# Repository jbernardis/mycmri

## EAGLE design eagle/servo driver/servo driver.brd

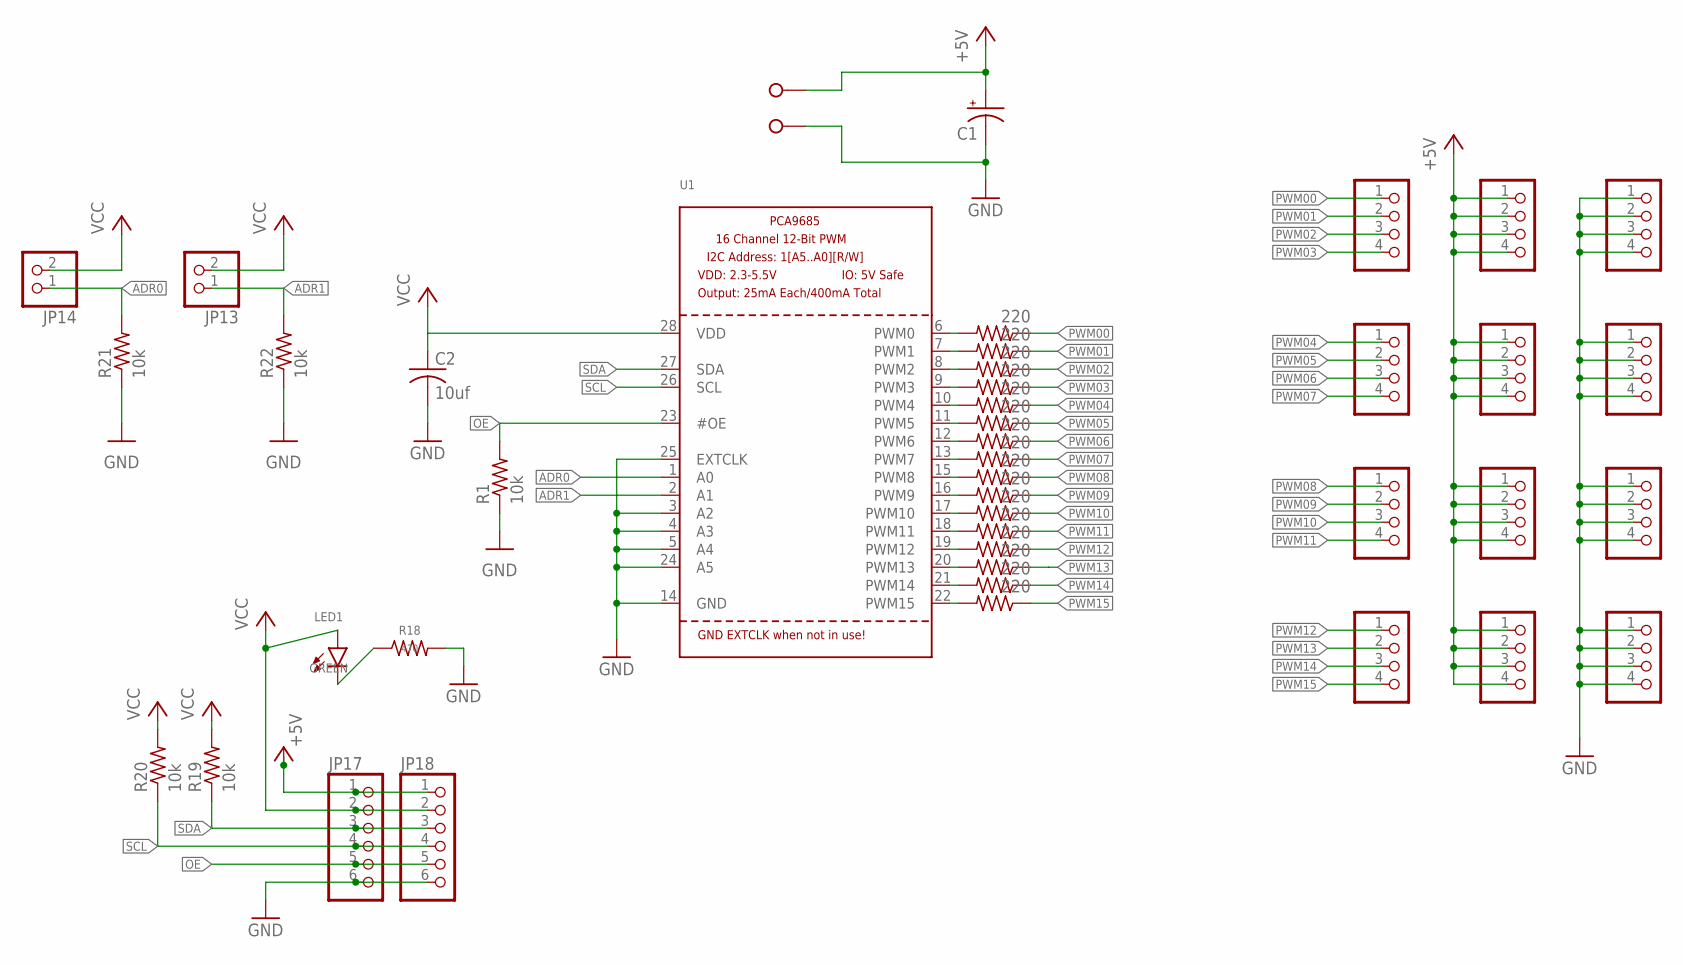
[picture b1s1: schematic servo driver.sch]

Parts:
C1: CPOL-USE5-8.5; E5-8,5
C2: 10uf; C025-024X044
JP1, JP2, JP3, JP4, JP5, JP6, JP7, JP8, JP9, JP10, JP11, JP12: PINHD-1X4; 1X04
JP13, JP14: PINHD-1X2; 1X02
JP17, JP18: PINHD-1X6CB; 1X06-CLEANBIG
LED1: GREEN; LED3MM
R1, R19, R20, R21, R22: 10k; 0207/10
R2, R3, R4, R5, R6, R7, R8, R9, R10, R11, R12, R13, R14, R15, R16, R17: 220; 0207/10
R18: 470; 0207/10
U1: PCA9685; TSSOP28
X1: W237-02P; W237-132

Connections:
+5V: C1.+, JP5.1, JP5.2, JP5.3, JP5.4, JP6.1, JP6.2, JP6.3, JP6.4, JP7.1, JP7.2, JP7.3, JP7.4, JP8.1, JP8.2, JP8.3, JP8.4, JP17.1, JP18.1, X1.1
ADR0: JP14.1, R21.2, U1.1 (A0)
ADR1: JP13.1, R22.2, U1.2 (A1)
GND: C1.-, C2.2, JP9.1, JP9.2, JP9.3, JP9.4, JP10.1, JP10.2, JP10.3, JP10.4, JP11.1, JP11.2, JP11.3, JP11.4, JP12.1, JP12.2, JP12.3, JP12.4, JP17.6, JP18.6, R1.1, R18.2, R21.1, R22.1, U1.3 (A2), U1.4 (A3), U1.5 (A4), U1.14 (GND), U1.24 (A5), U1.25 (EXTCLK), X1.2
unnamed: R2.2, U1.6 (PWM0)
unnamed: R3.2, U1.7 (PWM1)
unnamed: R4.2, U1.8 (PWM2)
unnamed: R5.2, U1.9 (PWM3)
unnamed: R6.2, U1.10 (PWM4)
unnamed: R7.2, U1.11 (PWM5)
unnamed: R8.2, U1.12 (PWM6)
unnamed: R9.2, U1.13 (PWM7)
unnamed: R10.2, U1.15 (PWM8)
unnamed: R11.2, U1.16 (PWM9)
unnamed: R12.2, U1.17 (PWM10)
unnamed: R13.2, U1.18 (PWM11)
unnamed: R14.2, U1.19 (PWM12)
unnamed: R15.2, U1.20 (PWM13)
unnamed: R16.2, U1.21 (PWM14)
unnamed: R17.2, U1.22 (PWM15)
unnamed: LED1.K (C), R18.1
OE: JP17.5, JP18.5, R1.2, U1.23 (#OE)
PWM00: JP1.1, R2.1
PWM01: JP1.2, R3.1
PWM02: JP1.3, R4.1
PWM03: JP1.4, R5.1
PWM04: JP2.1, R6.1
PWM05: JP2.2, R7.1
PWM06: JP2.3, R8.1
PWM07: JP2.4, R9.1
PWM08: JP3.1, R10.1
PWM09: JP3.2, R11.1
PWM10: JP3.3, R12.1
PWM11: JP3.4, R13.1
PWM12: JP4.1, R14.1
PWM13: JP4.2, R15.1
PWM14: JP4.3, R16.1
PWM15: JP4.4, R17.1
SCL: JP17.4, JP18.4, R20.1, U1.26 (SCL)
SDA: JP17.3, JP18.3, R19.1, U1.27 (SDA)
VCC: C2.1, JP13.2, JP14.2, JP17.2, JP18.2, LED1.A, R19.2, R20.2, U1.28 (VDD)

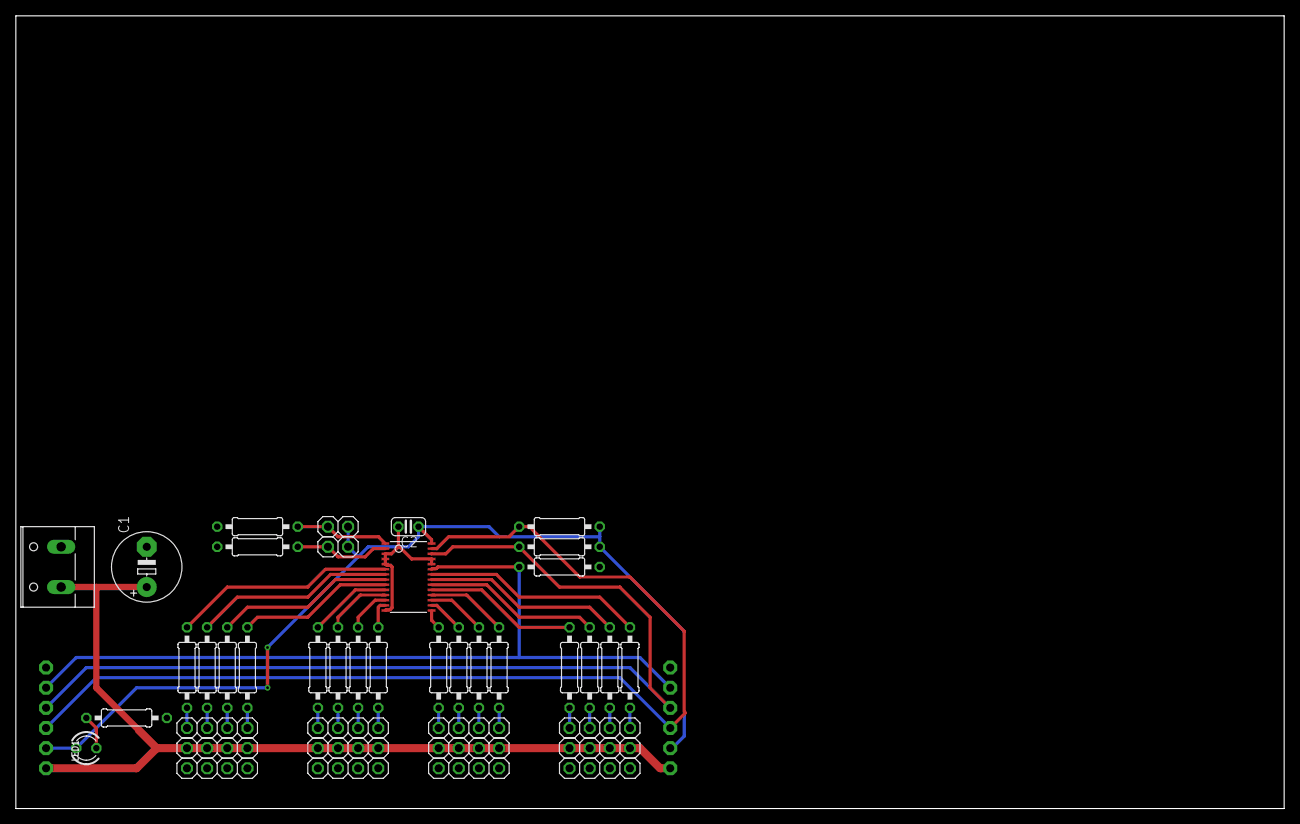
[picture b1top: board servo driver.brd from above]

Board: 2 copper layers, 160.0 x 100.0 mm, 43 parts (0 on the bottom side), 41 nets.
